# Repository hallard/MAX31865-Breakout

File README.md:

MAX31865 PT100, PT1000 RTD sensors Breakout board
=================================================

It's not the first time I want to measure sensors but one of the most used in industry are the PT100 and PT1000, and a friend of mine asked me several times to be able to easily measure temperature with these sensors. Here that breakout board

Detailed Description
====================

Everything is documented on this dedicated [post][1]

### Schematic  

### Boards  
&nbsp;
&nbsp;

##Library
When I created the MAX31865 breakout board, I needed a library to be able to read results. I then found one which was working file. I just added on it some features I needed, thank to Original library author olewolf.
- you can find the forked libray and sample code [here][3]

##Action
When all is fine, display temperature and Resistor value (reference also)    

and when there is a problem such as sensor not connected or breakout board not plugged   
&nbsp;

##License

<br /><span xmlns:dct="http://purl.org/dc/terms/" property="dct:title">MAX31865 PT100, PT1000 RTD Sensors Breakout Board</span> by <a xmlns:cc="http://creativecommons.org/ns#" href="https://hallard.me/max31865" property="cc:attributionName" rel="cc:attributionURL">Charles-Henri Hallard</a> is licensed under a <a rel="license" href="http://creativecommons.org/licenses/by-nc-sa/4.0/">Creative Commons Attribution-NonCommercial-ShareAlike 4.0 International License</a>.<br />Based on a work at <a xmlns:dct="http://purl.org/dc/terms/" href="https://github.com/hallard/MAX31865-Breakout" rel="dct:source">https://github.com/hallard/MAX31865-Breakout</a>.

##Misc
See news and other projects on my [blog][2] 
 
[1]: http://hallard.me/max31865/
[2]: http://hallard.me
[3]: https://github.com/hallard/arduino-max31865/

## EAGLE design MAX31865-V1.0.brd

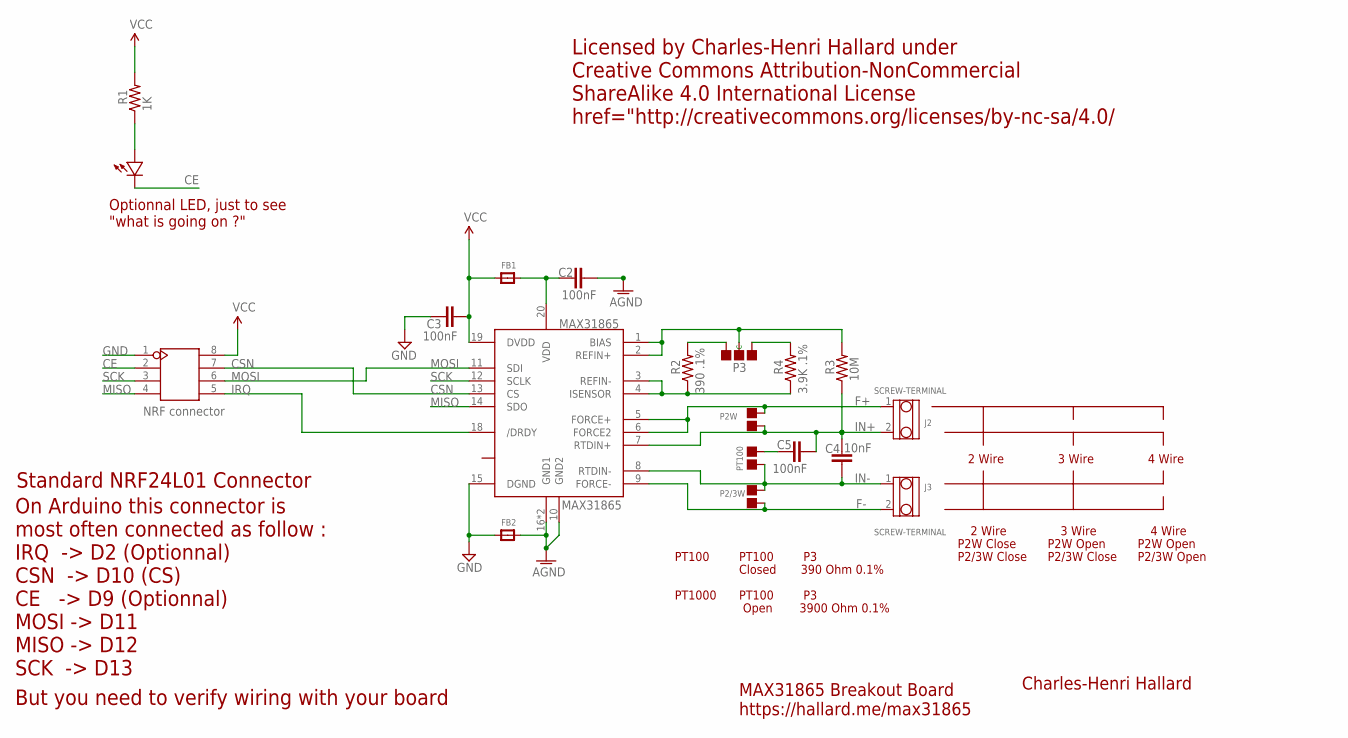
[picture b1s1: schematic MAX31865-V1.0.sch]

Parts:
C2, C3, C5: 100nF; 0603-CAP
C4: 10nF; 0603-CAP
FB1, FB2: FERRITE_0603MP; _0603MP
J1: NRF connector; 2X4P-2.54
J2, J3: SCREW-TERMINAL; 2P-3.5
MAX31865: MAX31865; TQFN20-5X5
P2/3W: 4 Wire; 2P-SMD-1.78X1.27
P2W: 3 Wire; 2P-SMD-1.78X1.27
P3: PAD-JUMPER-3P-40*40; 3P-SMD-4.1X1.5
PT100: PAD-JUMPER-2P; 2P-SMD-1.78X1.27
R1: 1K; 0603-RES
R2: 390 .1%; 0805-RES
R3: 10M; 0603-RES
R4: 3.9K .1%; 0805-RES
U$1: LED0805-LARGE; 0805-LED-LARGEPADS

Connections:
AGND: C2.2, FB2.2, MAX31865.10 (GND2), MAX31865.16 (GND1), MAX31865.EXP (GND1)
AVDD: C2.1, FB1.2, MAX31865.20 (VDD)
CE: J1.2, U$1.MINUS
CSN: J1.7, MAX31865.13 (CS)
F+: J2.1, MAX31865.5 (FORCE+), MAX31865.6 (FORCE2), P2W.2
F-: J3.2, MAX31865.9 (FORCE-), P2/3W.1
GND: C3.2, FB2.1, J1.1, MAX31865.15 (DGND)
IN+: C4.1, C5.2, J2.2, MAX31865.7 (RTDIN+), P2W.1, R3.1
IN-: C4.2, J3.1, MAX31865.8 (RTDIN-), P2/3W.2, PT100.1
IRQ: J1.5, MAX31865.18 (/DRDY)
MISO: J1.4, MAX31865.14 (SDO)
MOSI: J1.6, MAX31865.11 (SDI)
unnamed: R1.1, U$1.PLUS
unnamed: P3.11 (R), R2.2
unnamed: MAX31865.3 (REFIN-), MAX31865.4 (ISENSOR), R2.1, R4.1
unnamed: MAX31865.1 (BIAS), MAX31865.2 (REFIN+), P3.MM (C), R3.2
unnamed: P3.00 (L), R4.2
unnamed: C5.1, PT100.2
SCK: J1.3, MAX31865.12 (SCLK)
VCC: C3.1, FB1.1, J1.8, MAX31865.19 (DVDD), R1.2

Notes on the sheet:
MAX31865 Breakout Board https://hallard.me/max31865
Charles-Henri Hallard
Optionnal LED, just to see "what is going on ?"
Standard NRF24L01 Connector
PT100
Closed
390 Ohm 0.1%
PT1000
Open
3900 Ohm 0.1%
2 Wire
P2W Close
P2/3W Close
3 Wire
4 Wire
P2W Open
P2/3W Open
On Arduino this connector is most often connected as follow : IRQ -> D2 (Optionnal) CSN -> D10 (CS) CE -> D9 (Optionnal) MOSI -> D11 MISO -> D12 SCK -> D13
But you need to verify wiring with your board
Licensed by Charles-Henri Hallard under Creative Commons Attribution-NonCommercial ShareAlike 4.0 International License href="http://creativecommons.org/licenses/by-nc-sa/4.0/

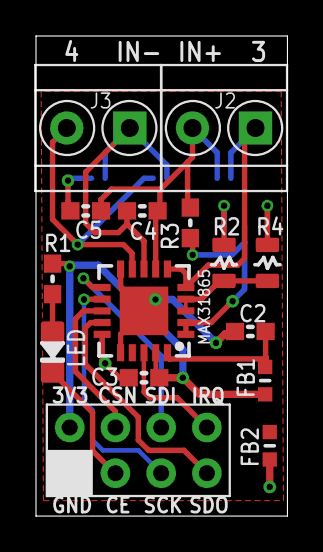
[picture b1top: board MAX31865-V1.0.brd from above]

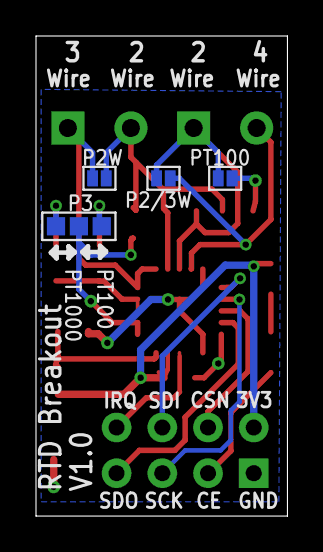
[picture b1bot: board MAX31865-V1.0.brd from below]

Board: 2 copper layers, 14.0 x 26.7 mm, 19 parts (4 on the bottom side), 20 nets.

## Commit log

2015-07-16 :neckbeard: Added .gitattributes
2015-07-16 Creation
2015-07-16 Link Error
2015-07-16 switched to 600dpi
2015-07-16 Added some pictures
2015-07-16 Pictures link error
2015-07-16 Pictures Resizing
2015-07-16 Picture size
2015-07-17 Added small picture
2016-06-07 Removed version number from filename

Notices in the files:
parts and their libraries:
microbuilder: This work is placed in the public domain, and may be freely used for commercial and non-commercial work with the following conditions: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
